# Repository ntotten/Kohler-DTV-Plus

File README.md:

# Kohler DTV+

Analysis of the Kohler DTV+ system controller (K-99695-NA / K-99693-P-NA), and a
working replacement interface for it.

> ⚠️ **Read [DISCLAIMER.md](DISCLAIMER.md) before running anything here.** This
> drives water temperature and flow on undocumented, unauthenticated hardware.
> Water above **43 °C / 109 °F can scald**, and some controller endpoints can
> brick the unit. Not affiliated with, endorsed by, or supported by Kohler Co.

## Why

The K-99693 wall interface on this system failed. The controller still reports
every other component as healthy — valve, amplifier, controller all `conn` — and
simply has nothing left to command it:

```
num_interface        = 0
ui1_con_string       = not_seen      <- the failed touchscreen
valve_1_con_string   = conn
amp_con_string       = conn
controller_con_string = conn
```

The controller exposes an undocumented CGI API that its own web pages use. That
is the replacement input.

## What's here

|                                                            |                                                                                                                                                                                                                              |
| ---------------------------------------------------------- | ---------------------------------------------------------------------------------------------------------------------------------------------------------------------------------------------------------------------------- |
| [app/](app/)                                               | React + Vite interface styled after the K-99693. Runs on a dev machine, a LAN box, or a phone browser.                                                                                                                       |
| [controller/](controller/)                                 | The replacement master — a Rust service driving the two Saturn valve buses from a Raspberry Pi, with its design docs, [build order](controller/docs/BUILD-ORDER.md), and parts list in [controller/docs/](controller/docs/). |
| [viewer/](viewer/)                                         | Separate 3D parts viewer and STL exporter for modification work. No hardware surface — it cannot touch the valve.                                                                                                            |
| [PROTOCOL.md](PROTOCOL.md)                                 | The controller's CGI API — transport quirks, endpoints, payload fields, safety ratings.                                                                                                                                      |
| [DESIGN.md](DESIGN.md)                                     | Architecture, decisions, testing, and what the Android/Capacitor port needs.                                                                                                                                                 |
| [DISCLAIMER.md](DISCLAIMER.md)                             | Safety warnings, CGI risk scale, and how this repo enforces it.                                                                                                                                                              |
| [LICENSE.md](LICENSE.md)                                   | Open Maker License, plus what it does and does not cover.                                                                                                                                                                    |
| [CONTRIBUTING.md](CONTRIBUTING.md) / [CLA.md](CLA.md)      | How to contribute safely, and the contributor agreement.                                                                                                                                                                     |
| [AGENT.md](AGENT.md) / [CLAUDE.md](CLAUDE.md)              | Contract for agents working here, including the story-log convention.                                                                                                                                                        |
| [STORY-LOG.md](STORY-LOG.md)                               | Significant events and reversals, newest first.                                                                                                                                                                              |
| [INVESTIGATIONS.md](INVESTIGATIONS.md)                     | What we are still trying to find out, and the experiments queued to find it out.                                                                                                                                             |
| [docs/](docs/)                                             | Kohler controller reference — hardware, firmware update pipeline, CGI surface, security posture, what firmware extraction would take.                                                                                        |
| [research/SOURCES.md](research/SOURCES.md)                 | Monitoring index — where to sweep for new community findings.                                                                                                                                                                |
| [research/FIELD-NOTES.md](research/FIELD-NOTES.md)         | What breaks when you automate a DTV+ — failure reports from the community, sourced, with what we changed in response.                                                                                                        |
| [research/diagnostics/](research/diagnostics/)             | Raw controller captures, dated — error logs, idle baselines, and the extraction probe.                                                                                                                                       |
| [research/reference-links.md](research/reference-links.md) | Bibliography — projects, integrations, Kohler documents, FCC exhibits, patents, platform sources.                                                                                                                            |
| [research/controller-mirror/](research/controller-mirror/) | Verbatim mirror of the controller's own web UI, plus live payload captures.                                                                                                                                                  |
| [research/xagon0/](research/xagon0/)                       | Vendored third-party analysis — see [PROVENANCE.md](research/xagon0/PROVENANCE.md).                                                                                                                                          |
| [research/reference/](research/reference/)                 | Kohler's user guide, rendered for interface reference.                                                                                                                                                                       |

## Quick start

```bash
cd app
npm install
npm run dev            # http://localhost:5180, and on your LAN IP
```

Set `KOHLER_HOST` if your controller is not at `192.168.0.115`.

```bash
npm test               # unit tests, no hardware
npm run selftest       # live checks, strictly read-only — never opens a valve
```

See [app/README.md](app/README.md) for hosting, the API surface, and the safety
gate.

The parts viewer is a separate app with its own dependencies and no connection
to the controller:

```bash
cd viewer
npm install
npm run dev            # http://localhost:5181
npm run check          # typecheck + tests + export gate + build
```

See [viewer/README.md](viewer/README.md) for why manufacturer CAD needs its
units declared, and what the K-99693 model turned out to be missing.

Formatting is repo-wide and mechanical, run from the root:

```bash
npm install
npm run format         # Markdown, TypeScript, CSS, YAML, HTML, JSON
npm run format:check   # what CI would check
```

## Safety gate

The controller has no authentication and exposes endpoints that can wipe or
brick it. Every known endpoint is rated 0-5 in
[app/server/cgi-safety.mjs](app/server/cgi-safety.mjs), and the proxy refuses
anything above **2/5** before a packet is sent. Only a subset of the ~50 known
endpoints is reachable; `reset_factory.cgi`, `clear_dt.cgi`, `fileupload.cgi`,
`unpack_bin.cgi`, `edit_dt.cgi`, `rpc.cgi` and friends are permanently
unreachable.

The live surface is the authority, not this page — `GET /api/safety` returns the
risk ceiling and the exact set of exposed endpoints.

## Hardware

The DTV+ system controller board — photograph by
[xagon0](https://github.com/xagon0/Kohler-DTV-Plus/blob/master/Images/Images.md),
re-encoded from the upstream 11 MB PNG to a 962 KB WebP at full 3710×2242
resolution (see [research/xagon0/PROVENANCE.md](research/xagon0/PROVENANCE.md)).
The controller
speaks RS-485 to the valve and amplifier, and HTTP/0.9-flavoured CGI to
everything else; [PROTOCOL.md](PROTOCOL.md) covers the latter.

## Credits

This repository began as a fork of
[timelery/Kohler-DTV-Plus](https://github.com/timelery/Kohler-DTV-Plus) (2017) by
Tim Elery — the original CGI enumeration and controller notes, which are
preserved in [PROTOCOL.md](PROTOCOL.md). It was detached from that fork network
on 2026-07-26, having diverged into a different project; the full history,
including Tim's original commits, is kept here intact.

- [xagon0/Kohler-DTV-Plus](https://github.com/xagon0/Kohler-DTV-Plus) — CGI
  safety ratings, RS-485 protocol analysis, hardware and repair documentation.
- [dcmeglio/kohler-python](https://github.com/dcmeglio/kohler-python) — endpoint
  and parameter reference.
- Kohler's _User Guide — Digital Interface and System Controller for DTV+_
  (1241234-5-D) for the interface design.

## License

Work original to this repository is under the
[Open Maker License](https://github.com/aaronse/OpenMakerLicense) — AGPL-3.0 with
a maker addendum. Personal, educational, repair, and small-shop use are
explicitly allowed; hosted-service and commercial redistribution need a licence.

The third-party material vendored here — xagon0's analysis, Kohler's guide and
controller UI, and the content inherited from `timelery` — is **not** covered and
is **not** ours to license. See [LICENSE.md](LICENSE.md) for the scope table.

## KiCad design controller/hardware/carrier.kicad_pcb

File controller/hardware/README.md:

# controller/hardware — the carrier: schematic, board and cabling

Revision B's carrier: a two-layer PCB that holds the Pico 2, the WIZ850io and
the five THVD1410 ports, and the cables between it, the K-99695, the valves and
the panel. What they draw is specified in [HARDWARE.md](../docs/HARDWARE.md);
where the two disagree, HARDWARE.md is right and the drawings are regenerated.

Every file here is generated. The scripts in `tools/` are the source of the
schematic and of the board, and nobody edits either in KiCad: change a table at
the top of a script and run `tools/render.sh`, which regenerates everything and
checks it.

| File                                       | What it is                                                                                                |
| ------------------------------------------ | --------------------------------------------------------------------------------------------------------- |
| [carrier.svg](carrier.svg)                 | The schematic, rendered by KiCad                                                                          |
| [fab/](fab/README.md)                      | What to order and how to build it: Gerber and drill zip, BOM, pick-and-place, drawings                    |
| [cabling.svg](cabling.svg)                 | Every cable between the carrier, the K-99695, the valves and the panel                                    |
| [cabling-wires.csv](cabling-wires.csv)     | The same, one row per conductor, with the pin and signal at each end                                      |
| `carrier.kicad_sch`, `carrier.kicad_sym`   | The schematic and the project's own symbols: Pico 2, the WIZ850io's two rows, THVD1410                    |
| `carrier.kicad_pcb`                        | The board                                                                                                 |
| `carrier.kicad_pro`, `carrier.kicad_dru`   | The project: design rules, net classes and one custom DRC rule                                            |
| `carrier.pretty/`                          | The project's own footprints: the Pico 2 and the WIZ850io in their sockets, and the Würth valve jack      |
| `carrier.ses`                              | Freerouting's routing, kept so the board rebuilds without routing again                                   |
| `sym-lib-table`                            | Points KiCad at `carrier.kicad_sym`                                                                       |
| [cabling.wireviz.yml](cabling.wireviz.yml) | The cabling's source, for [WireViz](https://github.com/wireviz/WireViz) 0.4                               |
| `tools/carrier_schematic.py`               | Writes the schematic from its tables: GPIO map, jack pins, ports, parts and part numbers                  |
| `tools/check_netlist.py`                   | Checks the netlist KiCad reads back against those tables                                                  |
| `tools/carrier_footprints.py`              | Writes `carrier.pretty` from the Pico 2 datasheet, WIZnet's dimension drawing and Würth's jack data sheet |
| `tools/carrier_board.py`                   | Places, routes (replaying `carrier.ses`), pours ground and runs DRC, which must find nothing              |
| `tools/carrier_fab.py`                     | Writes `fab/`                                                                                             |
| `tools/wire_list.py`                       | Writes `cabling-wires.csv` and checks the cabling against the board's nets                                |
| `tools/render.sh`                          | Runs all of it in order, and checks every Mermaid diagram in the repository                               |

```bash
pip install wireviz==0.4.1           # needs Graphviz: brew install graphviz
controller/hardware/tools/render.sh  # KiCad 7; --check fails if anything committed is stale
```

`render.sh` needs `kicad-cli` and a Python that can import KiCad's `pcbnew`
(`KICAD_CLI` and `KICAD_PYTHON` override where it looks; on a Mac it finds
both inside KiCad.app). The committed files were made with KiCad 7.0.11, and
rerunning it with that version reproduces every one byte for byte; another
version makes the same board in different bytes.

Routing is the one step that isn't repeatable: Freerouting finds a different
route each run. So `carrier.ses` holds its result and every run replays it.
After a change to the placement or the netlist, route again with
`render.sh --reroute`, which needs Freerouting 2.4.1 (`FREEROUTING_JAR`) and
Java 25 (`JAVA`), and commit the new `carrier.ses` with the board.

[docs/diagrams.md](../../docs/diagrams.md) is the convention for every drawing
in this repository.

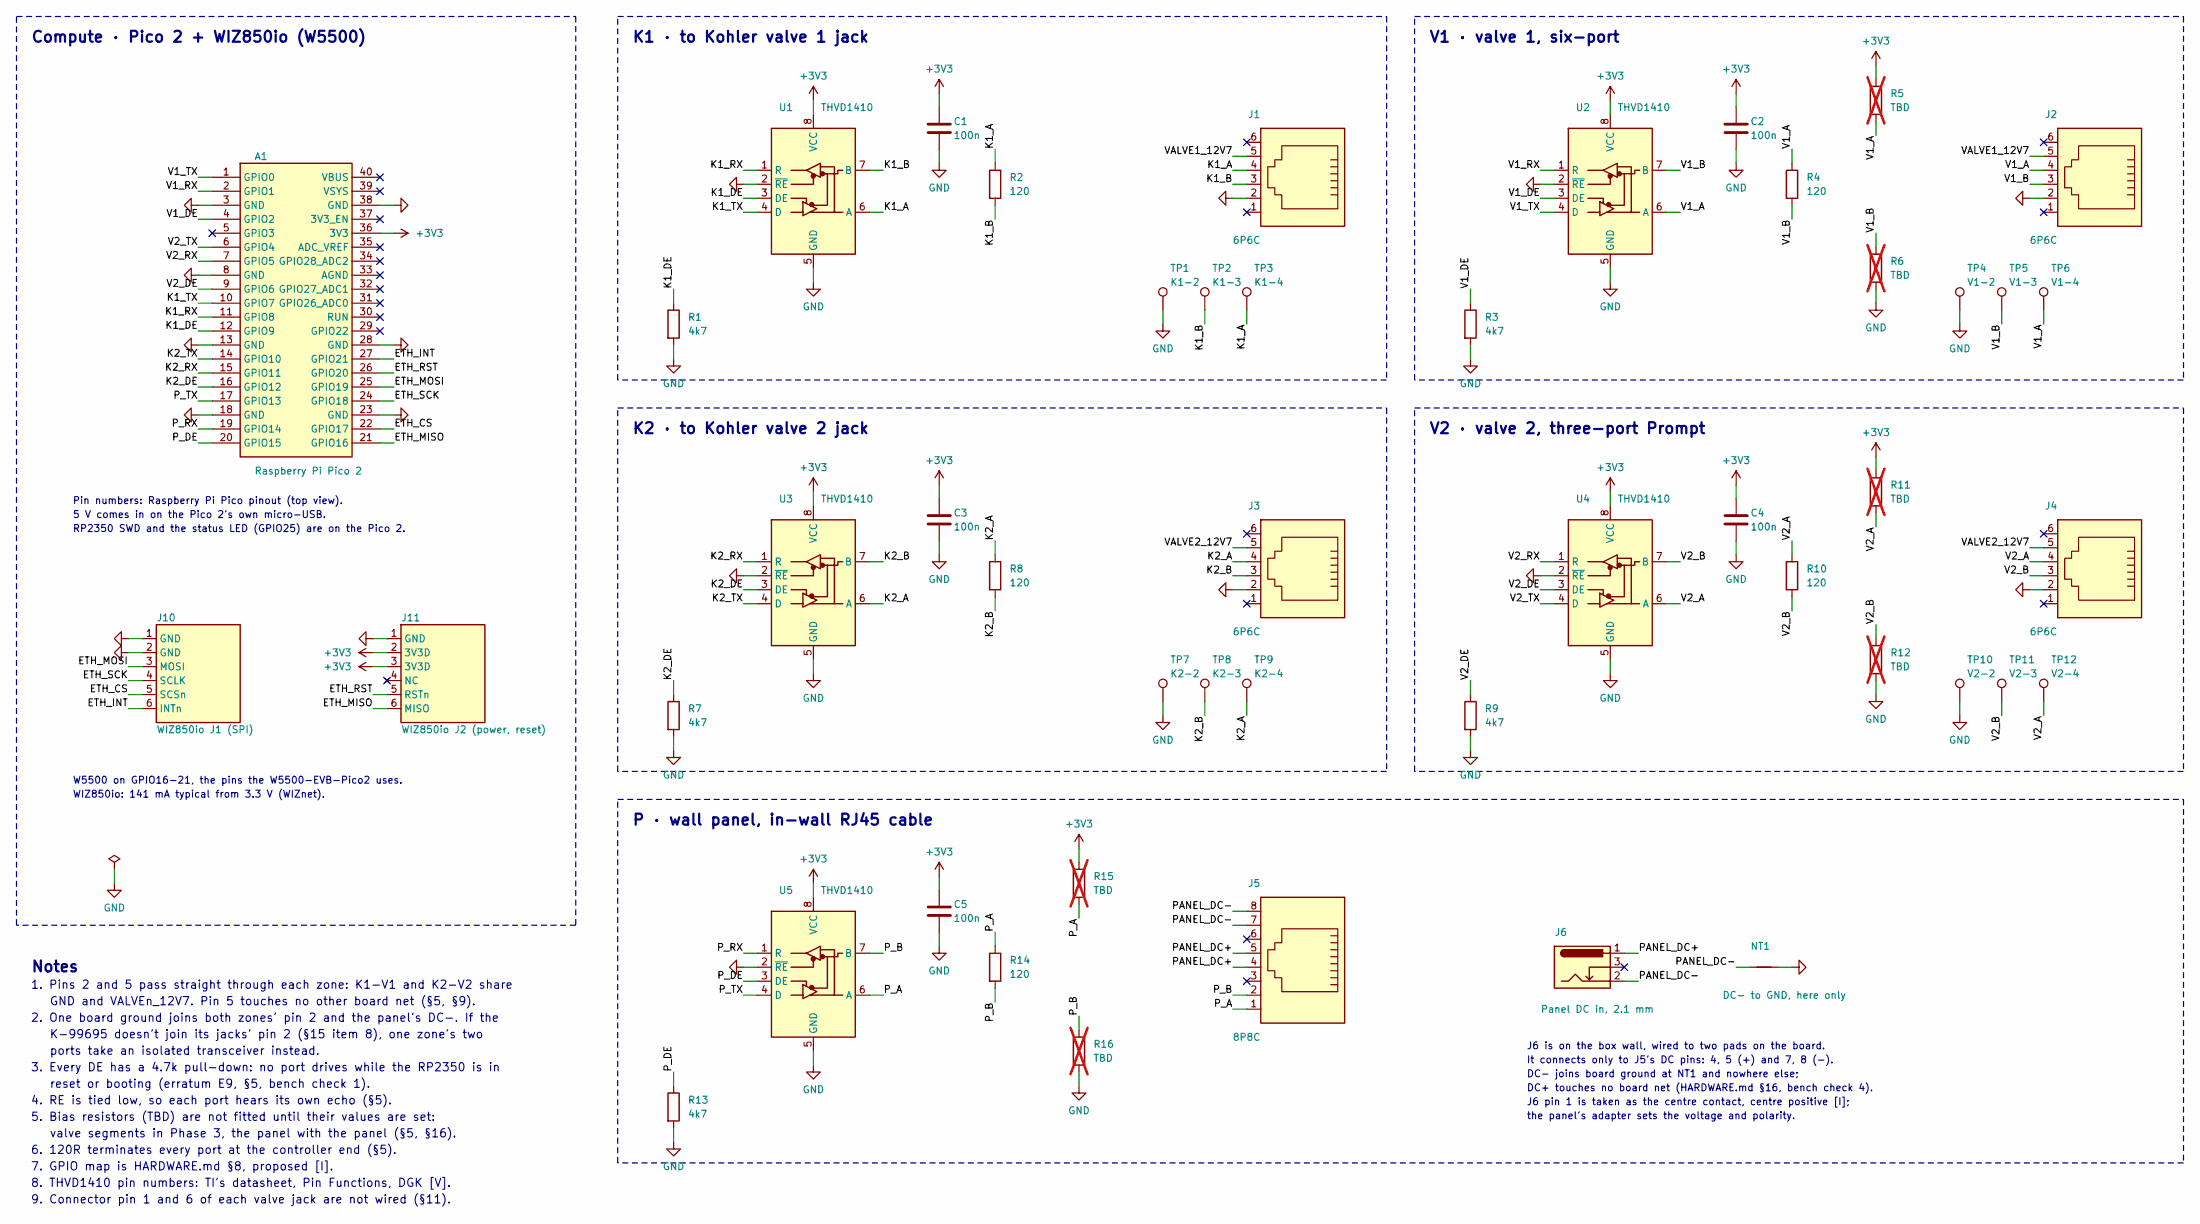
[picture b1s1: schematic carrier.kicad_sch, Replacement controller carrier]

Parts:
A1: Raspberry Pi Pico 2; Pico2_Socketed; MPN SC1631
C1, C2, C3, C4, C5: 100n; C_Rect_L4.0mm_W2.5mm_P2.50mm; MPN K104K15X7RF5TL2
J1, J2, J3, J4: 6P6C; RJ12_Wurth_615006138421_Horizontal; MPN 615006138421
J5: 8P8C; RJ45_Amphenol_54602-x08_Horizontal; MPN 54602-908LF
J6: Panel DC in, 2.1 mm; SolderWire-0.5sqmm_1x02_P4.8mm_D0.9mm_OD2.3mm; MPN 721A
J10: WIZ850io J1 (SPI); WIZ850io_J1; MPN WIZ850IO
J11: WIZ850io J2 (power, reset); WIZ850io_J2
NT1: DC- to GND, here only; NetTie-2_SMD_Pad0.5mm
R1, R3, R7, R9, R13: 4k7; R_Axial_DIN0207_L6.3mm_D2.5mm_P10.16mm_Horizontal; MPN CFR-25JB-52-4K7
R2, R4, R8, R10, R14: 120; R_Axial_DIN0207_L6.3mm_D2.5mm_P10.16mm_Horizontal; MPN CFR-25JB-52-120R
R5, R6, R11, R12, R15, R16: TBD; R_Axial_DIN0207_L6.3mm_D2.5mm_P10.16mm_Horizontal; not fitted
TP1: K1-2; PinHeader_1x01_P2.54mm_Vertical; MPN 1x1 male header, 2.54 mm
TP2: K1-3; PinHeader_1x01_P2.54mm_Vertical; MPN 1x1 male header, 2.54 mm
TP3: K1-4; PinHeader_1x01_P2.54mm_Vertical; MPN 1x1 male header, 2.54 mm
TP4: V1-2; PinHeader_1x01_P2.54mm_Vertical; MPN 1x1 male header, 2.54 mm
TP5: V1-3; PinHeader_1x01_P2.54mm_Vertical; MPN 1x1 male header, 2.54 mm
TP6: V1-4; PinHeader_1x01_P2.54mm_Vertical; MPN 1x1 male header, 2.54 mm
TP7: K2-2; PinHeader_1x01_P2.54mm_Vertical; MPN 1x1 male header, 2.54 mm
TP8: K2-3; PinHeader_1x01_P2.54mm_Vertical; MPN 1x1 male header, 2.54 mm
TP9: K2-4; PinHeader_1x01_P2.54mm_Vertical; MPN 1x1 male header, 2.54 mm
TP10: V2-2; PinHeader_1x01_P2.54mm_Vertical; MPN 1x1 male header, 2.54 mm
TP11: V2-3; PinHeader_1x01_P2.54mm_Vertical; MPN 1x1 male header, 2.54 mm
TP12: V2-4; PinHeader_1x01_P2.54mm_Vertical; MPN 1x1 male header, 2.54 mm
U1, U2, U3, U4, U5: THVD1410; VSSOP-8_3.0x3.0mm_P0.65mm; MPN THVD1410DGK

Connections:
+3V3: A1.36 (3V3), C1.1, C2.1, C3.1, C4.1, C5.1, J11.2 (3V3D), J11.3 (3V3D), R5.1, R11.1, R15.1, U1.8 (VCC), U2.8 (VCC), U3.8 (VCC), U4.8 (VCC), U5.8 (VCC)
/ETH_CS: A1.22 (GPIO17), J10.5 (SCSn)
/ETH_INT: A1.27 (GPIO21), J10.6 (INTn)
/ETH_MISO: A1.21 (GPIO16), J11.6 (MISO)
/ETH_MOSI: A1.25 (GPIO19), J10.3 (MOSI)
/ETH_RST: A1.26 (GPIO20), J11.5 (RSTn)
/ETH_SCK: A1.24 (GPIO18), J10.4 (SCLK)
/K1_A: J1.4, R2.1, TP3.1, U1.6 (A)
/K1_B: J1.3, R2.2, TP2.1, U1.7 (B)
/K1_DE: A1.12 (GPIO9), R1.1, U1.3 (DE)
/K1_RX: A1.11 (GPIO8), U1.1 (R)
/K1_TX: A1.10 (GPIO7), U1.4 (D)
/K2_A: J3.4, R8.1, TP9.1, U3.6 (A)
/K2_B: J3.3, R8.2, TP8.1, U3.7 (B)
/K2_DE: A1.16 (GPIO12), R7.1, U3.3 (DE)
/K2_RX: A1.15 (GPIO11), U3.1 (R)
/K2_TX: A1.14 (GPIO10), U3.4 (D)
/PANEL_DC+: J5.4, J5.5, J6.1
/PANEL_DC-: J5.7, J5.8, J6.2, NT1.1
/P_A: J5.1, R14.1, R15.2, U5.6 (A)
/P_B: J5.2, R14.2, R16.1, U5.7 (B)
/P_DE: A1.20 (GPIO15), R13.1, U5.3 (DE)
/P_RX: A1.19 (GPIO14), U5.1 (R)
/P_TX: A1.17 (GPIO13), U5.4 (D)
/V1_A: J2.4, R4.1, R5.2, TP6.1, U2.6 (A)
/V1_B: J2.3, R4.2, R6.1, TP5.1, U2.7 (B)
/V1_DE: A1.4 (GPIO2), R3.1, U2.3 (DE)
/V1_RX: A1.2 (GPIO1), U2.1 (R)
/V1_TX: A1.1 (GPIO0), U2.4 (D)
/V2_A: J4.4, R10.1, R11.2, TP12.1, U4.6 (A)
/V2_B: J4.3, R10.2, R12.1, TP11.1, U4.7 (B)
/V2_DE: A1.9 (GPIO6), R9.1, U4.3 (DE)
/V2_RX: A1.7 (GPIO5), U4.1 (R)
/V2_TX: A1.6 (GPIO4), U4.4 (D)
/VALVE1_12V7: J1.5, J2.5
/VALVE2_12V7: J3.5, J4.5
GND: A1.3 (GND), A1.8 (GND), A1.13 (GND), A1.18 (GND), A1.23 (GND), A1.28 (GND), A1.38 (GND), C1.2, C2.2, C3.2, C4.2, C5.2, J1.2, J2.2, J3.2, J4.2, J10.1 (GND), J10.2 (GND), J11.1 (GND), NT1.2, R1.2, R3.2, R6.2, R7.2, R9.2, R12.2, R13.2, R16.2, TP1.1, TP4.1, TP7.1, TP10.1, U1.2 (~RE), U1.5 (GND), U2.2 (~RE), U2.5 (GND), U3.2 (~RE), U3.5 (GND), U4.2 (~RE), U4.5 (GND), U5.2 (~RE), U5.5 (GND)

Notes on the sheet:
Compute · Pico 2 + WIZ850io (W5500)
Pin numbers: Raspberry Pi Pico pinout (top view).
5 V comes in on the Pico 2's own micro-USB.
RP2350 SWD and the status LED (GPIO25) are on the Pico 2.
W5500 on GPIO16-21, the pins the W5500-EVB-Pico2 uses.
WIZ850io: 141 mA typical from 3.3 V (WIZnet).
K1 · to Kohler valve 1 jack
V1 · valve 1, six-port
K2 · to Kohler valve 2 jack
V2 · valve 2, three-port Prompt
P · wall panel, in-wall RJ45 cable
J6 is on the box wall, wired to two pads on the board.
It connects only to J5's DC pins: 4, 5 (+) and 7, 8 (-).
DC- joins board ground at NT1 and nowhere else;
DC+ touches no board net (HARDWARE.md §16, bench check 4).
J6 pin 1 is taken as the centre contact, centre positive [I];
the panel's adapter sets the voltage and polarity.
Notes
1. Pins 2 and 5 pass straight through each zone: K1-V1 and K2-V2 share
GND and VALVEn_12V7. Pin 5 touches no other board net (§5, §9).
2. One board ground joins both zones' pin 2 and the panel's DC-. If the
K-99695 doesn't join its jacks' pin 2 (§15 item 8), one zone's two
ports take an isolated transceiver instead.
3. Every DE has a 4.7k pull-down: no port drives while the RP2350 is in
reset or booting (erratum E9, §5, bench check 1).
4. RE is tied low, so each port hears its own echo (§5).
5. Bias resistors (TBD) are not fitted until their values are set:
valve segments in Phase 3, the panel with the panel (§5, §16).
6. 120R terminates every port at the controller end (§5).
7. GPIO map is HARDWARE.md §8, proposed [I].
8. THVD1410 pin numbers: TI's datasheet, Pin Functions, DGK [V].
9. Connector pin 1 and 6 of each valve jack are not wired (§11).

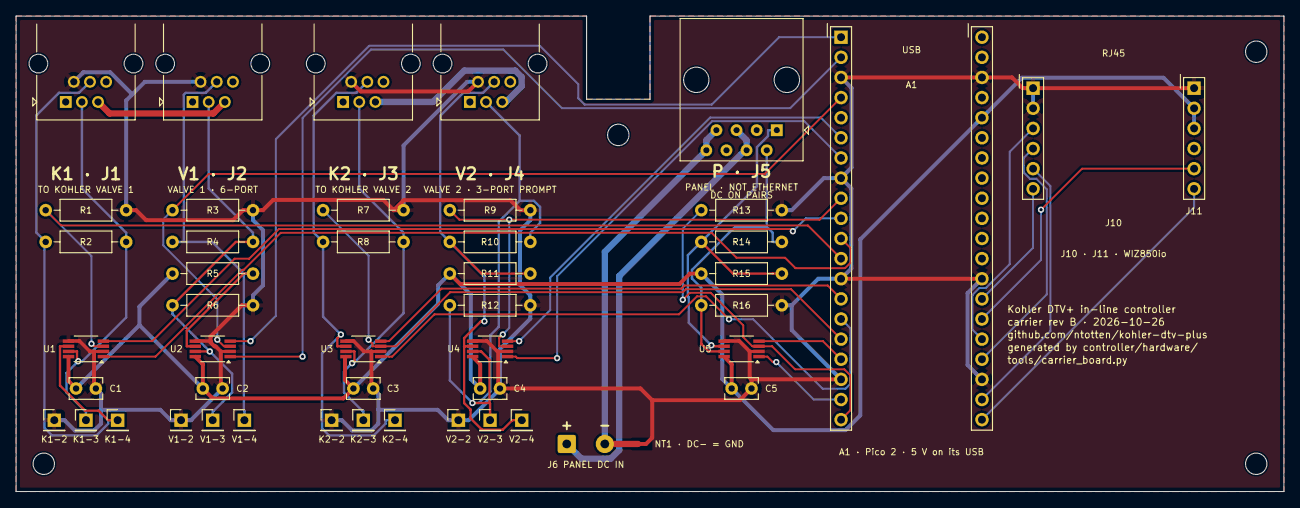
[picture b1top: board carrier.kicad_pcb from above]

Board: 2 copper layers, 160.0 x 60.0 mm, 52 parts (0 on the bottom side), 37 nets.

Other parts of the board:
H1, H2, H3, H4: M2.5; MountingHole_2.7mm_M2.5

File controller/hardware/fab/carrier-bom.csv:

Item,Qty,References,Value,Footprint,Manufacturer,MPN,Supplier,Fitted,Notes
1,1,A1,Raspberry Pi Pico 2,Pico2_Socketed,Raspberry Pi,SC1631,DigiKey 2648-SC1631CT-ND,yes,"2 x 1x20 female header, Sullins PPPC201LFBN-RC (DigiKey S7053-ND)"
2,5,C1 C2 C3 C4 C5,100n,C_Rect_L4.0mm_W2.5mm_P2.50mm,Vishay,K104K15X7RF5TL2,DigiKey BC1084CT-ND,yes,
3,4,J1 J2 J3 J4,6P6C,RJ12_Amphenol_54601-x06_Horizontal,Amphenol ICC,54601-906LF,"DigiKey, product 7589414",yes,
4,1,J5,8P8C,RJ45_Amphenol_54602-x08_Horizontal,Amphenol ICC,54602-908LF,DigiKey 609-1046-ND,yes,
5,1,J6,"Panel DC in, 2.1 mm",SolderWire-0.5sqmm_1x02_P4.8mm_D0.9mm_OD2.3mm,Switchcraft,721A,DigiKey SC3508-ND,yes,Box wall; two wires to the board's J6 pads
6,1,J10 J11,WIZ850io J1 (SPI),WIZ850io_J1,WIZnet,WIZ850IO,DigiKey 1278-1043-ND,yes,"1x6 female header, 2.54 mm, cut from a PPPC201LFBN-RC"
7,5,R1 R3 R7 R9 R13,4k7,R_Axial_DIN0207_L6.3mm_D2.5mm_P10.16mm_Horizontal,Yageo,CFR-25JB-52-4K7,DigiKey 13-CFR-25JB-52-4K7-ND,yes,
8,5,R2 R4 R8 R10 R14,120,R_Axial_DIN0207_L6.3mm_D2.5mm_P10.16mm_Horizontal,Yageo,CFR-25JB-52-120R,DigiKey 120QBK-ND,yes,
9,12,TP1 TP2 TP3 TP4 TP5 TP6 TP7 TP8 TP9 TP10 TP11 TP12,Test point,PinHeader_1x01_P2.54mm_Vertical,,"1x1 male header, 2.54 mm",Already owned,yes,
10,5,U1 U2 U3 U4 U5,THVD1410,VSSOP-8_3.0x3.0mm_P0.65mm,Texas Instruments,THVD1410DGK,Mouser 595-THVD1410DGK,yes,
11,0,R5 R6 R11 R12 R15 R16,TBD,R_Axial_DIN0207_L6.3mm_D2.5mm_P10.16mm_Horizontal,,,,no (DNP),

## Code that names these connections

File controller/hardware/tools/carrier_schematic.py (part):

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# HARDWARE.md §8. Pico 2 physical pin -> net. Pin numbers per Raspberry Pi's
# Pico pinout, which the Pico 2 keeps (KiCad's RaspberryPi_Pico symbol).
PICO_PINS = {
    1: ("GPIO0", "V1_TX"),
    2: ("GPIO1", "V1_RX"),
    3: ("GND", "GND"),
    4: ("GPIO2", "V1_DE"),
    5: ("GPIO3", None),
    6: ("GPIO4", "V2_TX"),
    7: ("GPIO5", "V2_RX"),
    8: ("GND", "GND"),
    9: ("GPIO6", "V2_DE"),
    10: ("GPIO7", "K1_TX"),
    11: ("GPIO8", "K1_RX"),
    12: ("GPIO9", "K1_DE"),
    13: ("GND", "GND"),
    14: ("GPIO10", "K2_TX"),
    15: ("GPIO11", "K2_RX"),
    16: ("GPIO12", "K2_DE"),
    17: ("GPIO13", "P_TX"),
    18: ("GND", "GND"),
    19: ("GPIO14", "P_RX"),
    20: ("GPIO15", "P_DE"),
    21: ("GPIO16", "ETH_MISO"),
    22: ("GPIO17", "ETH_CS"),
    23: ("GND", "GND"),
    24: ("GPIO18", "ETH_SCK"),
    25: ("GPIO19", "ETH_MOSI"),
    26: ("GPIO20", "ETH_RST"),
    27: ("GPIO21", "ETH_INT"),
    28: ("GND", "GND"),
    29: ("GPIO22", None),
    30: ("RUN", None),
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                     "Socket": "1x6 female header, 2.54 mm, cut from a PPPC201LFBN-RC"})
    for i, (_n, net) in enumerate(WIZ_J2, start=1):
        sh.connect("J11", i, net)
    sh.text("W5500 on GPIO16-21, the pins the W5500-EVB-Pico2 uses.", 22.86, 152.4)
    sh.text("WIZ850io: 141 mA typical from 3.3 V (WIZnet).", 22.86, 154.94)

    # Ground flag: the board's ground comes from the valves' pin 2 and the
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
